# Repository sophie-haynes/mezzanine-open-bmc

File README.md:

# mezzanine-open-bmc

This project contains the kicad files for the BMC project.

##Project Status
* _Schematic:_ Complete. Would be wise to have a quick review (just to be safe :) ).
* _PCB:_ Connected. DRC appears to throw some small issues, once resolved gerber files can be produced.
* _Footprints:_ Some footprints have been added to the project.

__NOTE:__ There is some strangeness between the schematic and PCB; the ratsnest shows incorrect connections in the PCB so be sure to refer to the schematic when connecting components.

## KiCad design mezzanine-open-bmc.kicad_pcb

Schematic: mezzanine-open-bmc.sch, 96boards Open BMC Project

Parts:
BT1: Battery CR2032; CR2032H
C1, C2: 39pF; C_0603
C3: 10uF; C_0603
C4, C11: 0.1uF; C_0603
C5, C7: 33u; C_1206
C6, C8: 0.1u; C_0603
C12, C13: 1uF; C_0603
CON1: USB_MICRO_B_ST-USB-001E
D1, D3, D5, D7: Led_Small; LED_0603
P1: CONN_02X20; Pin_Header_SMD_2x20_Pitch2mm; Mfr Part # F240-1220A0xMUx1
P2: CONN_02X20; Pin_Header_SMD_2x20_Pitch2mm; Mfr Part # P220-1220A0xMxxxx2
P3, P4, P5: CONN_01X04; Grove_SMD_Connector
R1, R13: 990R; R_0603
R2, R3: 220R; R_0603
R4: 10k; R_0603
R5, R6, R10, R17: 22R; R_0603
R7, R8: 0R; R_0603
R20: 10KΩ; R_0603
R22: 0R; R_1206
SW1: PWR; DIP_Toggle_Switch
SW2: RST; DIP_Toggle_Switch
U1: FT230XS; SSOP-16_3.9x4.9mm_Pitch0.635mm_Seeed
U2: PMIC-CJT1117-3.3(SOT223); SOT-223
U3: DS3231N; SO-16-W
U5: M24C16-WMN6P; SOIC127P600X175-8N
U6: REG_1.8V; SOT-23_Seeed; Mfr Part # XC6206P182MR

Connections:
+3V3: C7.1, C8.1, P3.3, P4.3, P5.3, U2.2, U3.2 (Vcc), U5.8; also elsewhere on the board
+3V3_F: C11.1, C12.1, U1.10 (3V3OUT), U1.11 (RESET), U6.3
/USB+: C1.1, CON1.3 (D+), R6.1, R6.2, U1.8 (USBD+)
/USB-: C2.1, CON1.2 (D-), R5.1, R5.2, U1.9 (USBD-)
CBUS0: U1.15 (CBUS0)
CBUS1: U1.14 (CBUS1)
GND: BT1.2, C1.2, C2.2, C3.2, C4.2, C5.2, C6.2, C7.2, C8.2, C11.2, C12.2, C13.2, CON1.5 (GND), CON1.6 (SHELL1), CON1.7 (SHELL2), CON1.8 (SHELL3), CON1.9 (SHELL4), D1.1 (K), D3.1 (K), D5.1 (K), D7.1 (K), P1.1, P1.2, P1.39, P1.40, P2.1, P2.2, P2.39, P2.40, P3.4, P4.4, P5.4, R20.1, SW1.2, SW2.2, U1.5 (GND), U1.13 (GND), U2.1, U3.5 (NC), U3.6 (NC), U3.7 (NC), U3.8 (NC), U3.9 (NC), U3.10 (NC), U3.11 (NC), U3.12 (NC), U3.13 (GND), U5.1, U5.2, U5.3, U5.4, U5.7, U6.1; also elsewhere on the board
GPIO_A: P1.23, P2.23
GPIO_B: P1.24, P2.24
GPIO_C: P2.25
GPIO_C_BMC: P1.25, R7.1
GPIO_D: P2.26
GPIO_D_BMC: P1.26, R8.1
GPIO_E: P2.27
GPIO_E_BMC: P1.27, R4.2
GPIO_F: P2.28
GPIO_F_BMC: P1.28
GPIO_G: P2.29
GPIO_G_BMC: P1.29
GPIO_H: P2.30
GPIO_H_BMC: P1.30
GPIO_I: P1.31, P2.31
GPIO_J: P1.32, P2.32
GPIO_K: P1.33, P2.33
GPIO_L: P1.34, P2.34
I2C0_SCL: P1.15, P2.15; also elsewhere on the board
I2C0_SCL_3.3: P3.1, U3.16 (SCL), U5.6; also elsewhere on the board
I2C0_SDA: P1.17, P2.17; also elsewhere on the board
I2C0_SDA_3.3: P3.2, U3.15 (SDA), U5.5; also elsewhere on the board
I2C1_SCL: P2.19; also elsewhere on the board
I2C1_SCL_3.3: P4.1; also elsewhere on the board
I2C1_SCL_BMC: P1.19; also elsewhere on the board
I2C1_SCL_BMC_3.3: P5.1; also elsewhere on the board
I2C1_SDA: P2.21; also elsewhere on the board
I2C1_SDA_3.3: P4.2; also elsewhere on the board
I2C1_SDA_BMC: P1.21; also elsewhere on the board
I2C1_SDA_BMC_3.3: P5.2; also elsewhere on the board
unnamed: BT1.1, U3.14 (Vbat)
unnamed: D1.2 (A), R1.2
unnamed: D3.2 (A), R10.2
unnamed: D5.2 (A), R13.2
unnamed: D7.2 (A), R17.2
unnamed: R2.2, U1.7 (CBUS2)
unnamed: R3.2, U1.16 (CBUS3)
unnamed: R20.2, U1.6 (CTS)
PCM_CLK: P2.18
PCM_CLK_BMC: P1.18
PCM_DI: P2.22
PCM_DI_BMC: P1.22
PCM_DO: P2.20
PCM_DO_BMC: P1.20
PCM_FS: P2.16
PCM_FS_BMC: P1.16
PWR_BTN_BMC: P1.4, R2.1, SW1.1
PWR_BTN_N: P2.4, R7.2
RST_BTN_BMC: P1.6, R3.1, SW2.1
RST_BTN_N: P2.6, R8.2
SPIO_CS: P2.12
SPIO_CS_BMC: P1.12
SPIO_DIN: P2.10
SPIO_DIN_BMC: P1.10
SPIO_DOUT: P2.14
SPIO_DOUT_BMC: P1.14
SPIO_SCL: P2.8
SPIO_SCL_BMC: P1.8
SYS_DCIN: P2.36, P2.38, R22.2
SYS_DCIN_BMC: P1.36, P1.38, R22.1
UART0_CTS: P2.3
UART0_RTS: P2.9
UART0_RX: P2.7
UART0_TX: P2.5
UART1_RX: P1.5, P2.13
UART1_RX_BMC: P1.13, U1.1 (TXD)
UART1_TX: P1.7, P2.11
UART1_TX_BMC: P1.11, U1.4 (RXD)
VBUS: C3.1, C4.1, CON1.1 (VBUS), U1.12 (VCC)

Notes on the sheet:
Pins connecting to BASEBOARD
Pins for BMC
BMC Power and Reset Switches
BB PWR/RST to BMC GPIO
Baseboard PWR LED's
Micro USB FTDI
5v-3.3v buck power converter
RTC
BMC PWR LED's
Decoupling Caps
EEPROM for I2C0
FTDI Regulator

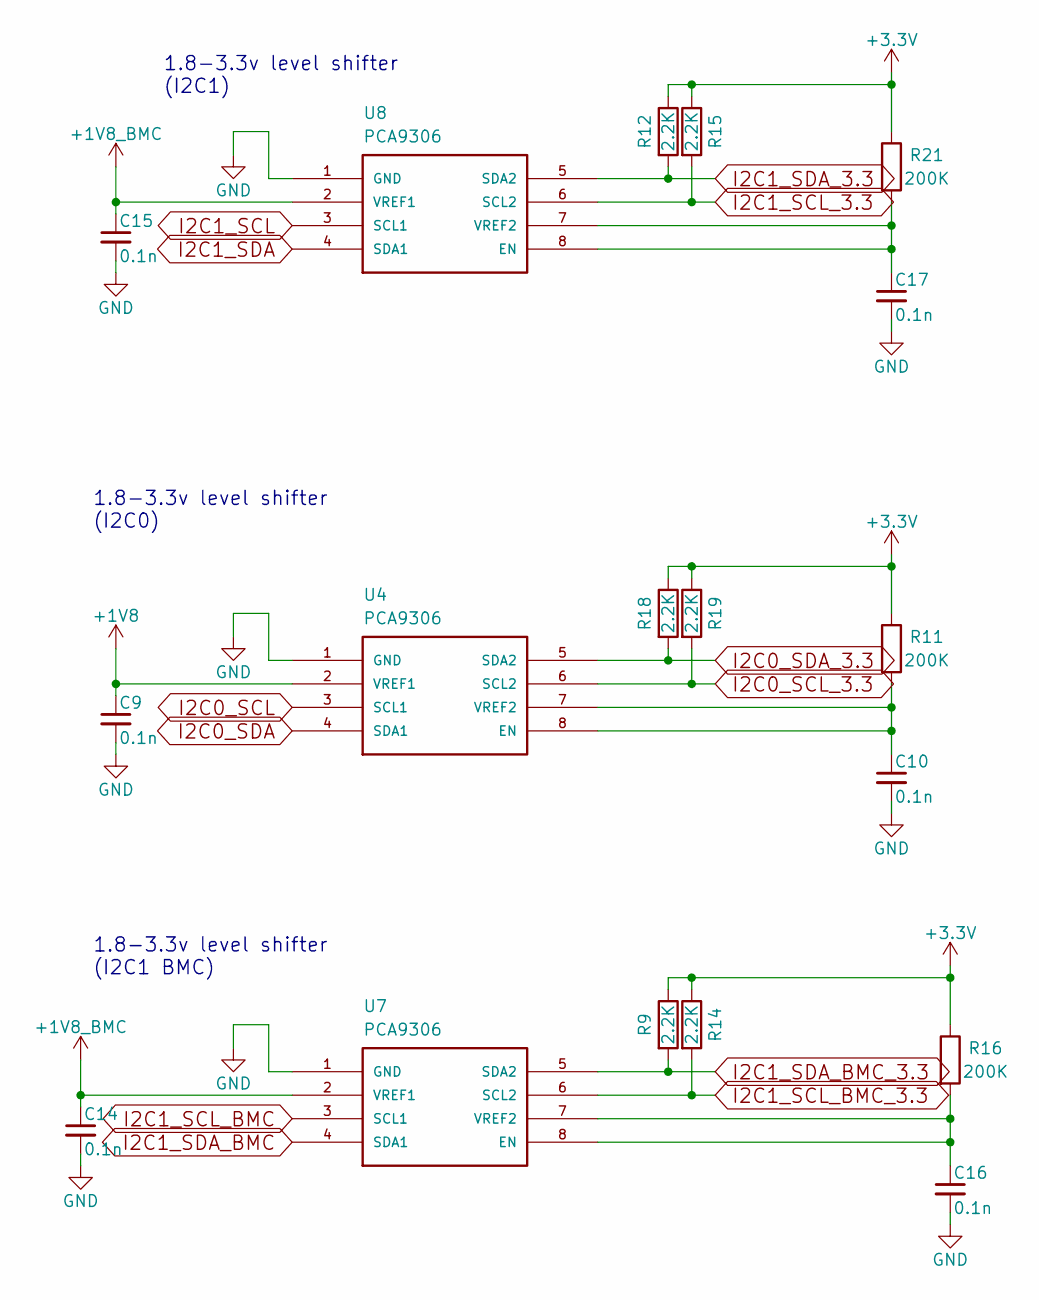
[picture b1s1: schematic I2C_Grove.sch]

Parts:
C9, C10, C14, C15, C16, C17: 0.1n; C_0603
R9, R12, R14, R15, R18, R19: 2.2K; R_0603
R11, R16, R21: 200K; R_0603
U4, U7, U8: PCA9306

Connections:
+3V3: R9.1, R11.1, R12.1, R14.1, R15.1, R16.1, R18.1, R19.1, R21.1; also elsewhere on the board
GND: C9.2, C10.2, C14.2, C15.2, C16.2, C17.2, U4.1 (GND), U7.1 (GND), U8.1 (GND); also elsewhere on the board
I2C0_SCL: U4.3 (SCL1); also elsewhere on the board
I2C0_SCL_3.3: R19.2, U4.6 (SCL2); also elsewhere on the board
I2C0_SDA: U4.4 (SDA1); also elsewhere on the board
I2C0_SDA_3.3: R18.2, U4.5 (SDA2); also elsewhere on the board
I2C1_SCL: U8.3 (SCL1); also elsewhere on the board
I2C1_SCL_3.3: R15.2, U8.6 (SCL2); also elsewhere on the board
I2C1_SCL_BMC: U7.3 (SCL1); also elsewhere on the board
I2C1_SCL_BMC_3.3: R14.2, U7.6 (SCL2); also elsewhere on the board
I2C1_SDA: U8.4 (SDA1); also elsewhere on the board
I2C1_SDA_3.3: R12.2, U8.5 (SDA2); also elsewhere on the board
I2C1_SDA_BMC: U7.4 (SDA1); also elsewhere on the board
I2C1_SDA_BMC_3.3: R9.2, U7.5 (SDA2); also elsewhere on the board
unnamed: C10.1, R11.2, U4.7 (VREF2), U4.8 (EN)
unnamed: C16.1, R16.2, U7.7 (VREF2), U7.8 (EN)
unnamed: C17.1, R21.2, U8.7 (VREF2), U8.8 (EN)

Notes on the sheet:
1.8-3.3v level shifter (I2C1)
1.8-3.3v level shifter (I2C0)
1.8-3.3v level shifter (I2C1 BMC)

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
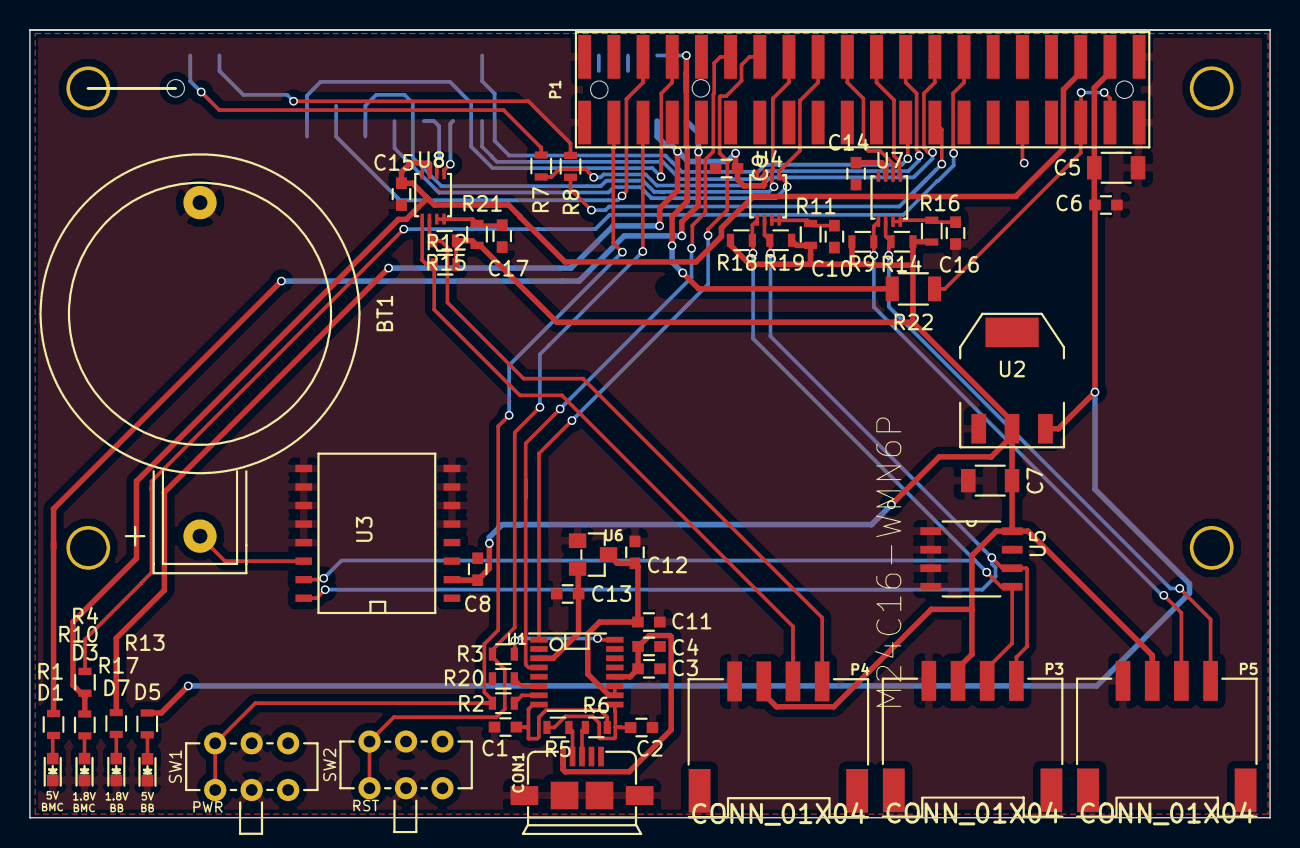
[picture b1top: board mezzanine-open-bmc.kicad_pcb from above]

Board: 2 copper layers, 85.0 x 54.0 mm, 60 parts (1 on the bottom side), 50 nets.

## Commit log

2016-03-01 Initial Commit
    Initial Commit
2016-03-01 Connect BB UART1 to BMC UART1
    All pins on the BMC header pins now have "_BMC" appended to their signal
    names. This is to allow connections to be made from different pins on the
    BB (Baseboard).
    UART1 on the BB is now connected to UART1 on the BMC
2016-03-01 Connect BB GPIO_A/B to BMC GPIO_A/B
    GPIO A & B are now connected on the BB to the BMC.
2016-03-01 Connect BB PWR/RST to BMC GPIO
    The BB PWR BTN is now wired to BMC GPIO C.
    BB RST BTN is wired to BMC GPIO D.
2016-03-01 Connect BB 1V8 to BMC GPIO_E, Make New Library
    The BB 1V8 is wired up to BMC GPIO_E.
2016-03-01 Connect FTDI to BMC UART1
    A microUSB is now connected to UART1.
2016-03-10 Change Signal Names for GPIO_A/B BMC
    Since GPIO_A and GPIO_B are to be connected on the BB & BMC pins,
    the signal names have been renamed to match.
2016-03-10 Add 22R to GPIO_B_BMC, Add to BMC Lib
    To protect the board, a resistor has been added to the GPIO line
2016-03-10 Add PCA9306 and Connect SCL, SDA
2016-03-10 Add Decoupling Caps to FTDI
    Decoupling capacitors were missing from the schematic. These have been added
    (including footprints).
2016-03-12 WIP: Wire Up Level Shifter
    Work in progress
2016-03-15 Add Level Shifter to Schematic
    First attempt at wiring up pca9306 level shifter to the I2C buses.
    VCC power is likely to be wrong.
2016-03-18 Add HS Conn. Footprint
    Very simple footprint for the FCI 61083-061***
    Measurements might be slightly off.
2016-03-22 Append New Schematic to Current Working Schematic
    A new schematic containing a level shifter (1.8v-3.3v), buck power converter
    (5v-3.3v) and RTC.
    This is a rough append; it is likely signal name changes will be required.
2016-03-25 Tidy sch lines and include new footprints, Assign footprints
    Changes:
    *Rename GPIO_A/B (remove BB_BMC)
    *Include footprints (SSOP-16, USB-MICRO, SOT-23)
    *Include decoupling caps
    *Add LED & transistor for 1v8 line
    *Fix shifted layout
2016-03-29 Add LED's to BMC PWR Lines
    LED's have been added to the BMC 5v & 1v8 power lines. This will indicate
    when the board is powered up.
2016-03-30 Assign More Footprints, Position Header
    This commit add footprints to switches and the High Speed Connector (PCA9306).
    In the PCB, the header pins are in the correct position now so that the two
    stacking HiKey boards will be attatched one the same side and power ports
    will be coming out of the same side.
2016-03-30 Group Components on PCB
    Components have been grouped in the PCB to make it tidier and make positioning
    easier.
2016-03-31 Add PDF Schematic
    This commit adds a pdf version of the schematic.
2016-04-04 Remove LED, Connect Remaining GPIO
    LED is not required for RTC unit so has been removed.
    The remaining unconnected GPIO have been connected so the the BMC board
    can access them,
2016-04-04 Change Value of C3 & C4
    Capacitor values for the decoupling capaitors have been
    changed to 10uF
2016-04-04 Remove PWR from FT230XS Pin 10, Add Capacitor
    Pin 10 already gets power from LDO, so additional 3v3
    power has been removed.
    Capacitor has been added for safety :)
    Decoupling caps has been moved closer to the VBUS signals
    to show they need to be close together.
2016-04-04 Pull Down CTS on FT230XS
    So that this pin is not "floating", it has been pulled down with a
    10KΩ resistor.
2016-04-04 Add Resistors to I2C0_SCL/SDA_3.3
    Acting as pull up registers
2016-04-05 Add LDO Footprint
    Regulator footprint for LDO 310030097 CJT1117-3.3 has been created.
2016-04-06 Change PWR Converter & Fix Library Issues/Confusing Jiggery Pokery
    This commit attempts to fix loading issues with libraries
    and footprints. The correct footprint for SOT-233 has been applied
    to the 5v-3v3 buck power converted and has been tweaked as needed.
2016-04-06 Connect Header Pins
    This is a first draft of the connections between the two header pins. This layout
    may not be the most efficient therefore is likely to be changed.
2016-04-11 [WIP] PCB
2016-04-11 Alternative Traces for Header Pins
    Since most components will be sitting on the top side of the
    device, traces for the header pins have been drawn on the bottom side
    as much as possible. This should mean it will be easier to connect the
    rest of the components.
    A new branch has been made to preserve the former trace layout if this
    version is no good.
2016-04-11 Add New Footprints and Assign to Transistors
    Footprints have been added to the .pretty folder.
    Footprint for the transistors Q1 & Q2 have been assigned.
2016-04-12 Add Footprint and Signal for EEPROM
    The M24C16-WDW6TP EEPROM has been added to the project. This will be used for
    the i2c lines on both devices.
2016-04-13 Add EEPROM for I2C Lines to Schematic
    First attempt at connecting i2c lines to EEPROM. Currently only connected to
    the BMC pins. This will be changed so it is also connected to the baseboard
    i2c
2016-04-13 Remove "_BMC" Suffix From I2C0 Lines
    To improve i2c connections with the EEPROM, signal names
    have been changed.
2016-04-15 Update PDF for Schematic
2016-04-20 Create Correct Footprint for PCA9306, Assign Footprint, Connect U4
    The PCA footprint was incorrect. This has been fixed; there are two
    different models so both types have been added. It has been assigned
    accordingly in the schematic.
    U4(level shifter 1.8-3.3v) has been connected up.
2016-04-20 Wire Up FTDI
    The wiring for the FTDI components have been connnected up in a neat
    little bundle which can be placed on the board.
2016-04-20 Wire Up BB LED (1.8v)
    The wiring for the LED components of 1.8 have been connnected up in a neat little
    bundle which can be placed on the board.
2016-04-20 Wire Up BMC LED's
    The wiring for the BMC PWR LED's have been connnected up in a neat
    little bundle which can be placed on the board.
2016-04-21 Start Track Layout
2016-04-21 Grant Tweaks
2016-04-23 Tidy LED (Schematic)
    LED's have been moved and wires aligned.
2016-04-24 Add Regulator for FTDI and Include 3V3_F in 96lib
    A 3v3 to 1v8 regulator has been added for the FTDI.
2016-04-24 Add Grove Connectors for I2C
    The two I2C lines have now been wired to two grove connectors and passed
    through level shifter to 5v
2016-04-24 Connect Up Components
    All components are connected (barring the battery since there is no
    footprint currently)
2016-04-25 Complete PCB Layout and Include Missing Footprints (BT1, C5, C7)
    The missing footprints have been added to both the schematic and the PCB.
    Capacitor values for C6 have been changes to 0.1uF.
    The new components have been connected up in the PCB.
2016-04-30 Change Grove Connectors to SMD
    Since this is a stacking board, it would be difficult to access
    upright connectors. Therefore. they have been changed to right angled grove
    connectors.
2016-05-02 Make Layout in SCH Pretty
    Grove connector layout have been redrawn into a heirarhcial sheet.
2016-05-03 Complete Schematic & Start PCB Layout
    Pulling all the changes in.
2016-05-04 Swap Location of P1/P2
    The BMC board should be on the top, so the pin header have been switched
    accordingly.
2016-05-04 Change Push Switches to Slide Toggle
    Since this is a stackable board, it could be awkward to access push buttons.
    These have been changed to sliders for usability.
2016-05-05 Position USB and Connect
    The USB is now positioned and all its important components are connected.
2016-05-05 Move Switches to Bottom of Board
2016-05-06 Position Grove Conn. Level Shifters
    All three LS for the grove Connecotrs have been placed in a nice
    layout in suitable location on board.
2016-05-08 [WIP] PCB In Progress
2016-05-13 [WIP]
    Updating the repository, still drawing traces.
2016-05-18 [WIP] Just several GPIO require connecting
    Most components are connected now. I dislike the bunching of traces, and some
    1v8 lines are quite long which is bad for interference.
    The bunching of all the traces so close to the pins is causing issues getting
    the last connectors connected. I may have to move the LS down, and move all the
    traces down too. :(
2016-05-18 [WIP] Just several GPIO require connecting
    Most components are connected now. I dislike the bunching of traces, and some
    1v8 lines are quite long which is bad for interference.
    The bunching of all the traces so close to the pins is causing issues getting
    the last connectors connected. I may have to move the regulators down,
    and move all the traces down too. :(
2016-06-02 Pull All Changes From Local Repository
    Updating the repo to include all local files.
    This commit completes wiring for the BMC board.
